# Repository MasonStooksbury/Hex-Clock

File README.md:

# Hex Clock | KiCad 9.0

From the mind of my good friend and inventor Johnathan Wood comes: the *Hex Clock*. A novel timepiece combining two of his favorite things: technology and hexagons. The Hex Clock uses two hexagons to represent sexigesimal, 24-hour time using two 6-bit binary numbers wrapped around hexagons. Let's see a picture that will hopefully make more sense. (And yes, the left-most bit of the hours hex will never be illuminated except during animations)

<br>

<br><br><br>

# Pre-setup Instructions
### Download these things (if you don't already have them)
- Download VSCode: [link](https://code.visualstudio.com/download)
- Install VSCode Extension `MicroPico` by paulober
- Download firmware for RaspberryPi PicoW (if you haven't already done this): [latest](https://rpf.io/pico-w-firmware)
- Download/Clone the code from this repo

<br><br><br>

# Developer Setup
- Open just the `PicoWCode` folder in VSCode; it should look something like this:
  - This is really important for a later step. Doing this wrong could have weird effects or just not work
  - 
- Plug in your PicoW (`pico` from now on)
- Under the `View` tab, click on `Command Palette...` or do `Ctrl + Shift + P` if that shortcut is enabled
- Click `MicroPico: Connect` to attempt a connection to the pico
- Once connected, you will see options appear in the footer bar of VSCode (you'll use these mostly):
  - 
- If all is good, you should see that checkmark with "Pico Connected" next to it
  - If this doesn't work, try replugging it, getting a different cable, or trying a different USB port
- Finally, open up the `test.py` file and make sure that you are on that tab (when we hit the `Run` footer button, MicroPico will attempt to run whatever tab we currently have focused)
- Click the `Run` footer button
- If you see "Everything is awesome!" in the terminal, then you're ready to start developing!

<br><br><br>

# Developing and Testing
### This will put all of your code onto the pico, and allow you to start testing
- Click the `All commands` footer button
- Click `MicroPico: Upload project to Pico`. This will put all of the files in the lefthand explorer onto the pico (this is why we need to open *only* the `PicoWCode` folder in VSCode)
- Once finished, it's often good to do a soft reset (no idea why, I've just noticed it help sometimes) simply click the `Reset` footer button
- Make sure that the `main.py` (or whatever `.py` file you are currently testing) is open and focused
- Click the `Run` footer button

<br>

## Quick and Dirty Testing
### If you just want to test code in a singular file (and don't really need everything else) you can simply focus the relevant file and hit the `Run` footer button. This is particularly helpful when developing new animations or random bits of code

### NOTE: If you're trying to test a file that imports another file (and you're changing both files regularly), this won't work and you'll have to follow the above instructions where you upload the code to the pico. 
  
<br><br><br>

# Connecting to the Pico and Using the Web App
### These instructions will help you connect to the Pico with your phone or other device and use the webapp that allows you to set the clock colors, change the time, or change the login credentials
- Either plug in the pico to an external power source or - if developing with VSCode open - connect the pico, open the main.py file, and click the `Run` footer button
- Once you see the `AP is active. You can now connect` message, the pico wifi access point (AP) is ready to receive connections
- Take note of the IP address listed just below this as you will need it in a moment (NOTE: In final version, this will hopefully be replaced with a domain name that you can connect to)
- On a wifi-enabled device, look for the `Hex Clock` network and connect to it (this is the default name and can be changed in the `main.py` script if desired)
- Once connected, open your web browser and type in the IP address from the previous step into the address bar
- At this point, you should see the Hex Clock login screen
- Login with these default credentials:
  - Username: `flump`
  - Password: `doople`

<br><br><br>

# Changing the Access Point SSID
- Changing the AP SSID is as simple as changing the line towards the top of `main.py`. However, the tricky part is in getting it propagate
- The steps below are about the only sure-fire way I've found to get it to work
  - Make sure the pico isn't currently running (if it is, click the `Stop` footer button to do so)
  - Click the `All commands` footer button
  - Click the `MicroPico: Delete all files from board` option
  - Click the `Reset` footer button
  - Physically unplug the pico from the computer
  - Plug the pico back in
  - Reconnect MicroPico manually or wait a second (it's usually pretty good about reconnecting automatically)
  - Click the `All commands` footer button
  - Click the `MicroPico: Upload project to Pico` option
  - Click the `Reset` footer button
  - On your wifi-enabled device that you are going to connect, go into your wifi settings and forget the network you previously attached to (this is critical as sometimes it will not show the SSID change on your device)
  - Click the `Run` footer button
  - At this point you should see the new SSID being broadcast under the available networks

<br><br><br>

# Troubleshooting
### These are some things I've run into and how to fix them
- Every now and then when you try to run `main.py` and the AP attempts to start up you might see this error: `OSError: [Errno 98] EADDRINUSE`. Follow these steps to mitigate it
  - If running, click the `Stop` footer button
  - Click the `Reset` footer button to perform a soft reset of the pico
  - Click the `Run` footer button again
  - If the above steps do not work, you can also just try click `Run` over and over again. Usually after 3-5 attempts it will work
- Sometimes when trying to hit the `Run` footer button you will see: `SyntaxError: invalid syntax`. Typically this just means that you have the wrong script focused. Make sure you are on the `main.py` script (or whatever script you're working on)

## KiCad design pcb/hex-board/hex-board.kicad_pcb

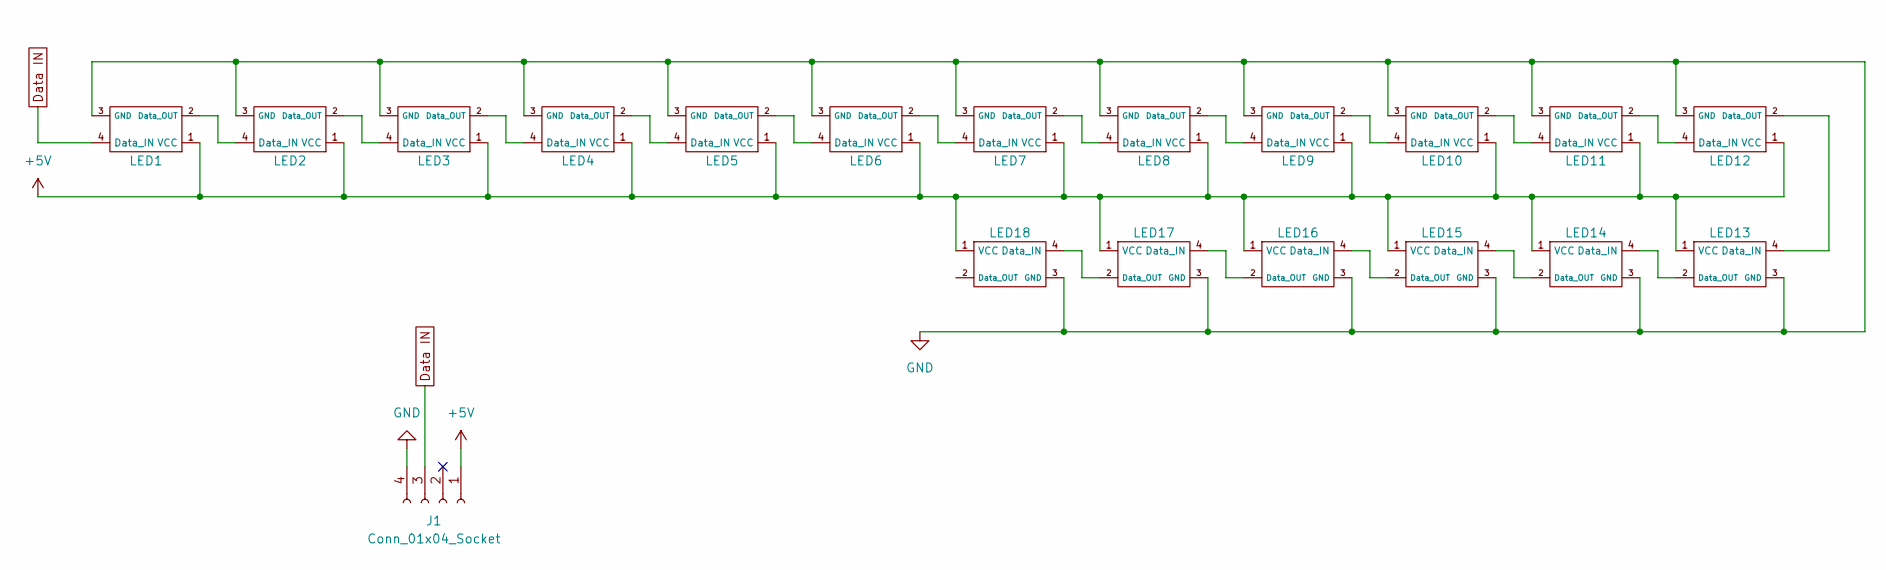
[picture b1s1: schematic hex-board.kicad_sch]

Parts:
J1: Conn_01x04_Socket; JST_EH_S4B-EH_1x04_P2.50mm_Horizontal
LED1, LED2, LED3, LED4, LED5, LED6, LED7, LED8, LED9, LED10, LED11, LED12, LED13, LED14, LED15, LED16, LED17, LED18: LED_SK6812RGBW_5050Metric_Pad1.5x1.5mm_HandSolder

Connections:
+5V: J1.1, LED1.1 (VCC), LED2.1 (VCC), LED3.1 (VCC), LED4.1 (VCC), LED5.1 (VCC), LED6.1 (VCC), LED7.1 (VCC), LED8.1 (VCC), LED9.1 (VCC), LED10.1 (VCC), LED11.1 (VCC), LED12.1 (VCC), LED13.1 (VCC), LED14.1 (VCC), LED15.1 (VCC), LED16.1 (VCC), LED17.1 (VCC), LED18.1 (VCC)
Data IN: J1.3, LED1.4 (Data_IN)
GND: J1.4, LED1.3 (GND), LED2.3 (GND), LED3.3 (GND), LED4.3 (GND), LED5.3 (GND), LED6.3 (GND), LED7.3 (GND), LED8.3 (GND), LED9.3 (GND), LED10.3 (GND), LED11.3 (GND), LED12.3 (GND), LED13.3 (GND), LED14.3 (GND), LED15.3 (GND), LED16.3 (GND), LED17.3 (GND), LED18.3 (GND)
unnamed: LED1.2 (Data_OUT), LED2.4 (Data_IN)
unnamed: LED2.2 (Data_OUT), LED3.4 (Data_IN)
unnamed: LED3.2 (Data_OUT), LED4.4 (Data_IN)
unnamed: LED4.2 (Data_OUT), LED5.4 (Data_IN)
unnamed: LED5.2 (Data_OUT), LED6.4 (Data_IN)
unnamed: LED6.2 (Data_OUT), LED7.4 (Data_IN)
unnamed: LED7.2 (Data_OUT), LED8.4 (Data_IN)
unnamed: LED8.2 (Data_OUT), LED9.4 (Data_IN)
unnamed: LED9.2 (Data_OUT), LED10.4 (Data_IN)
unnamed: LED10.2 (Data_OUT), LED11.4 (Data_IN)
unnamed: LED11.2 (Data_OUT), LED12.4 (Data_IN)
unnamed: LED12.2 (Data_OUT), LED13.4 (Data_IN)
unnamed: LED13.2 (Data_OUT), LED14.4 (Data_IN)
unnamed: LED14.2 (Data_OUT), LED15.4 (Data_IN)
unnamed: LED15.2 (Data_OUT), LED16.4 (Data_IN)
unnamed: LED16.2 (Data_OUT), LED17.4 (Data_IN)
unnamed: LED17.2 (Data_OUT), LED18.4 (Data_IN)

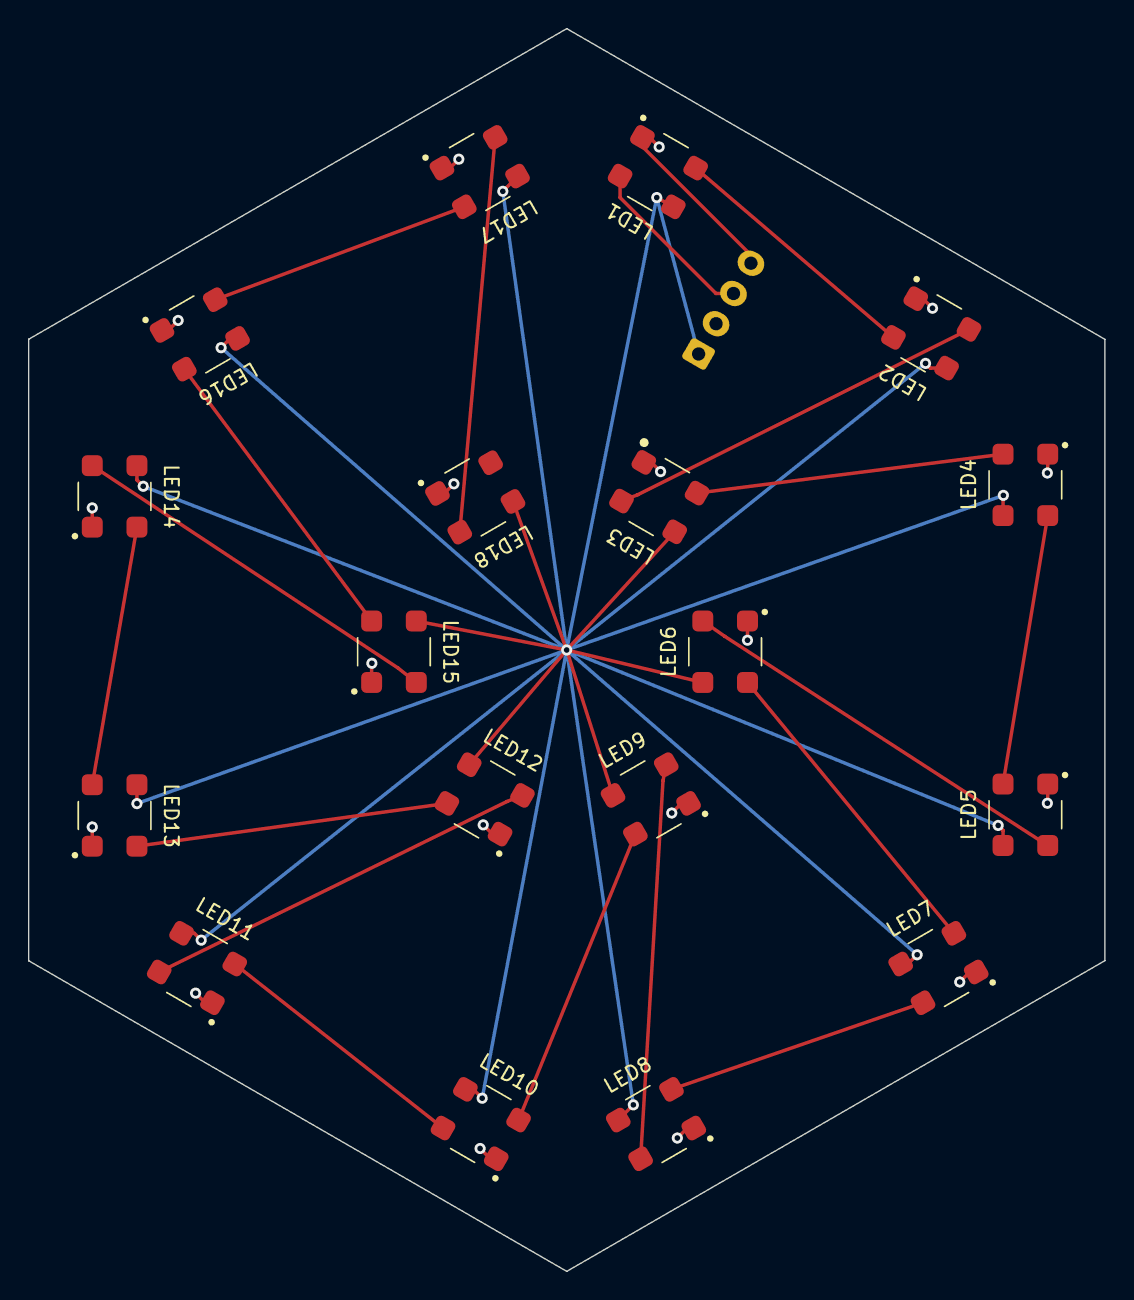
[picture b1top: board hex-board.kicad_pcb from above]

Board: 2 copper layers, 77.1 x 89.0 mm, 19 parts (1 on the bottom side), 20 nets.

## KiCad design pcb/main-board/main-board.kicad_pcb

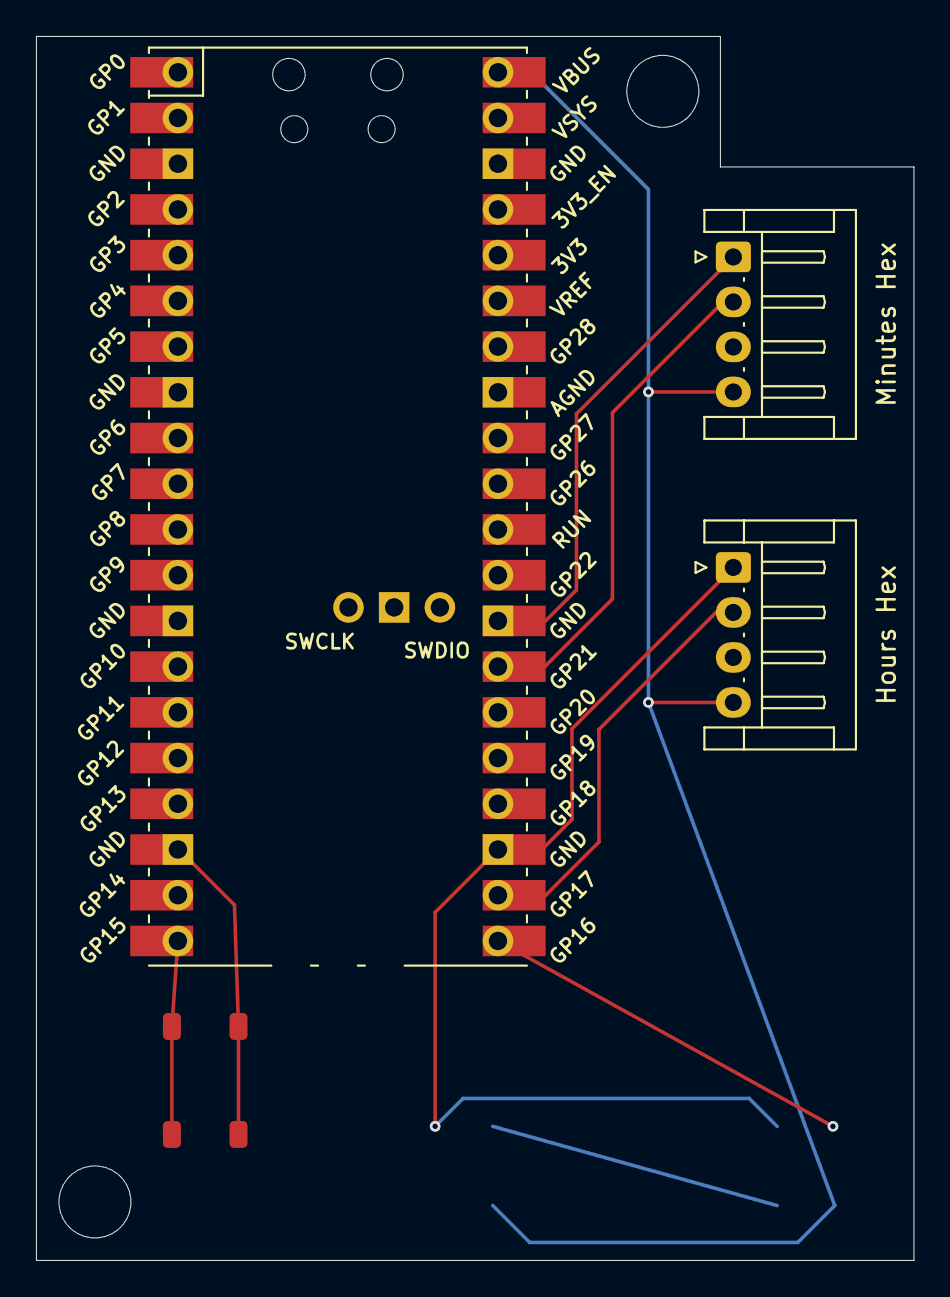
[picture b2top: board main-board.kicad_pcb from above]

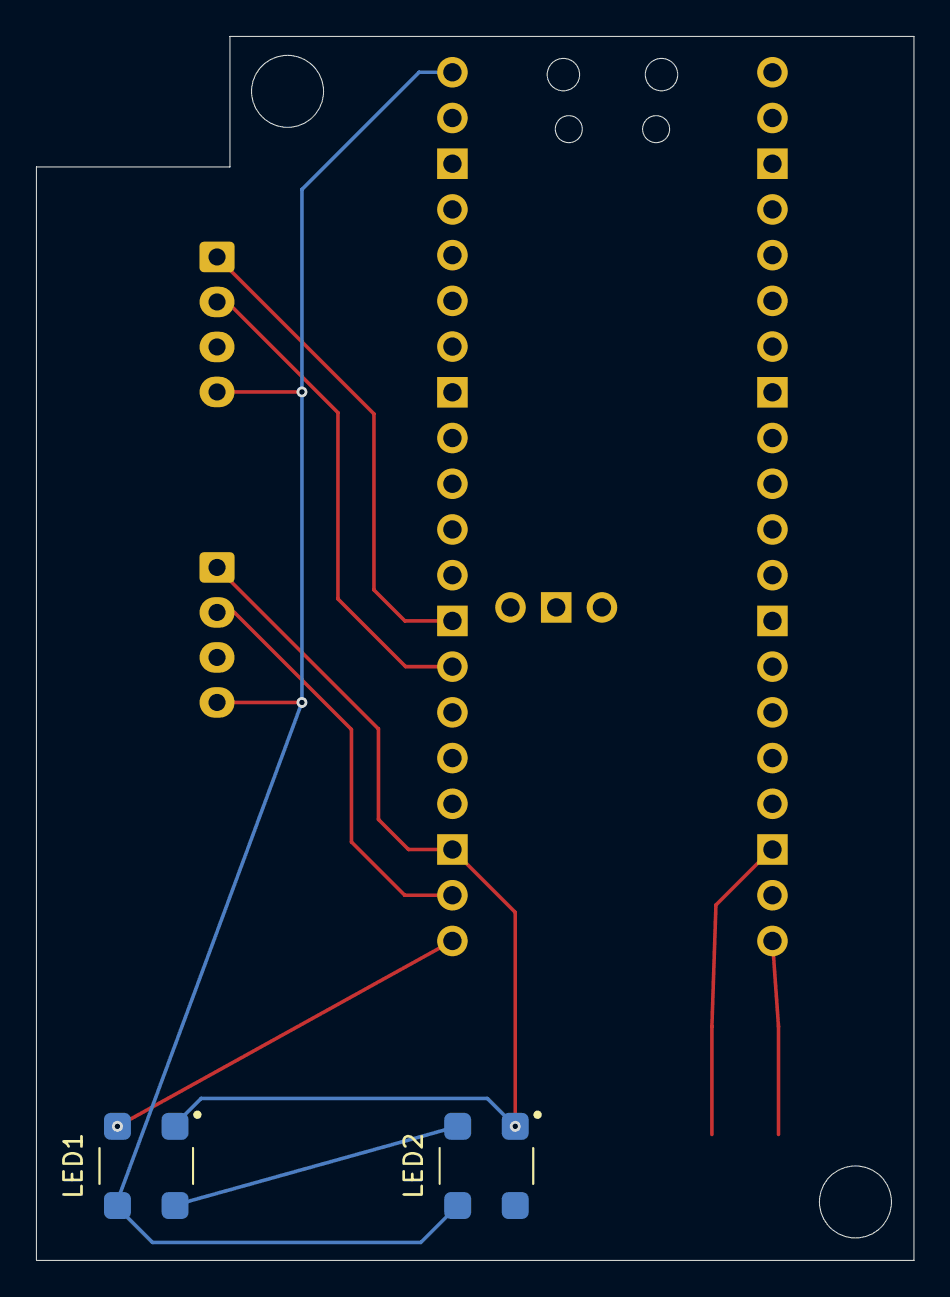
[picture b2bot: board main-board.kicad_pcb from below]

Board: 2 copper layers, 48.8 x 68.0 mm, 6 parts (2 on the bottom side), 9 nets.

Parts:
Hours Hex: Conn_01x04_Socket; JST_EH_S4B-EH_1x04_P2.50mm_Horizontal
LED1, LED2: LED_SK6812RGBW_5050Metric_Pad1.5x1.5mm_HandSolder
Minutes Hex: Conn_01x04_Socket; JST_EH_S4B-EH_1x04_P2.50mm_Horizontal
SW1: SW_Push; Switch
U1: PicoW; RPi_PicoW_SMD_TH

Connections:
unnamed: Minutes Hex.1, U1.28 (GND)
unnamed: Minutes Hex.2, U1.27 (GPIO21)
unnamed: Hours Hex.4, LED1.1 (VCC), LED2.1 (VCC), Minutes Hex.4, U1.40 (VBUS)
unnamed: Hours Hex.1, LED1.3 (GND), LED2.3 (GND), U1.23 (GND)
unnamed: Hours Hex.2, U1.22 (GPIO17)
unnamed: LED1.4 (Data_IN), U1.21 (GPIO16)
unnamed: LED1.2 (Data_OUT), LED2.4 (Data_IN)
unnamed: SW1.2, U1.18 (GND)
unnamed: SW1.1, U1.20 (GPIO15)

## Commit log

2023-11-19 Renaming files
2023-11-19 Added pads for DATA_IN and 5V
2023-11-21 Added ground pad
2023-11-26 Moving PCB stuff and adding PicoW code
2023-11-26 All tabs are now stubbed out. Need to add color picker to colors tab next
2023-11-27 Wired up hexes and got all screens sending back relevant info to the main Python script
2023-11-27 Added comments, moved script tag to script.js file
2023-11-27 Added toggle button to show current time. Got it all wired up to show correct colors when switching between current and preview time. Also added a dropdown with options for preset colors. Need to wir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
2023-12-01 Totally redoing everything from scratch. Got the AP working and serving pages. Just need to clean it up a little and work on a custom DNS
2023-12-01 Modified code so that there are fewer file reads. Fixed the short-write sending for page serving. And commented everything
2023-12-02 Added lots of code to get everything wired and working. Mostly the login page and security around the routing
2023-12-02 So many changes. I don't wanna type everything
2023-12-02 Moved password stuff around, AP starts without password, added entry/exit logic for AP mode. Code now starts in one mode and can switch to the other when you leave. Cleaned up some code, added commen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
2023-12-02 Added route protection to CSS and JS files for main
2023-12-06 Started adding LED code now that PCB is in and prepped
2023-12-15 Added necessary code to display a binary number on the PCB with a particular color. Also added comments to everything to be a bit more clear, as well as solved a bug in the animation code that was ca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
2023-12-20 Tons of documentation, a README, and some code
2023-12-20 Update README.md
    Adding picture links
2023-12-20 README Update
2023-12-20 Added new picture, README changes
2023-12-20 Added more sections to the readme
2023-12-20 readme updates
2023-12-21 Create LICENSE.md
    Adding CERN OHW v2 - Permissive license
2023-12-21 Adding licenses
2023-12-21 Adding badges to readme
2023-12-29 Added housing folder for when we do 3D stuff
2024-01-02 Added LambBrainz silkscreen logo. Added alignment dot for LEDs on silkscreen. Modified some traces
2024-05-21 Updated README with more dev information. Tested code to convert time to binary. Added most of the code for the new 'Set Date' section
2024-05-22 Finished date logic and RTC initialization code. Added some test animations to play around
2024-07-05 Moved everything around, renamed a bunch of stuff, started on the Main Board, and updated to KiCad 8
2024-07-05 Mostly finished main board, just need to add a password reset switch
2024-07-05 Fixing folder name case sensitivity issue
2024-07-05 Added switch
2024-07-06 Finished switch placement and wiring
2024-07-07 Added JST connector to hex board
2024-07-07 Added colon LEDs, moved stuff around the board, etc
2024-07-09 Added more space around mounting hole, added labels to JST connectors again
2024-11-05 Modifications
2026-01-22 Updating to 9.0

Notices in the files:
README.md:
License: CERN-OHL-P-2.0
License: MIT
